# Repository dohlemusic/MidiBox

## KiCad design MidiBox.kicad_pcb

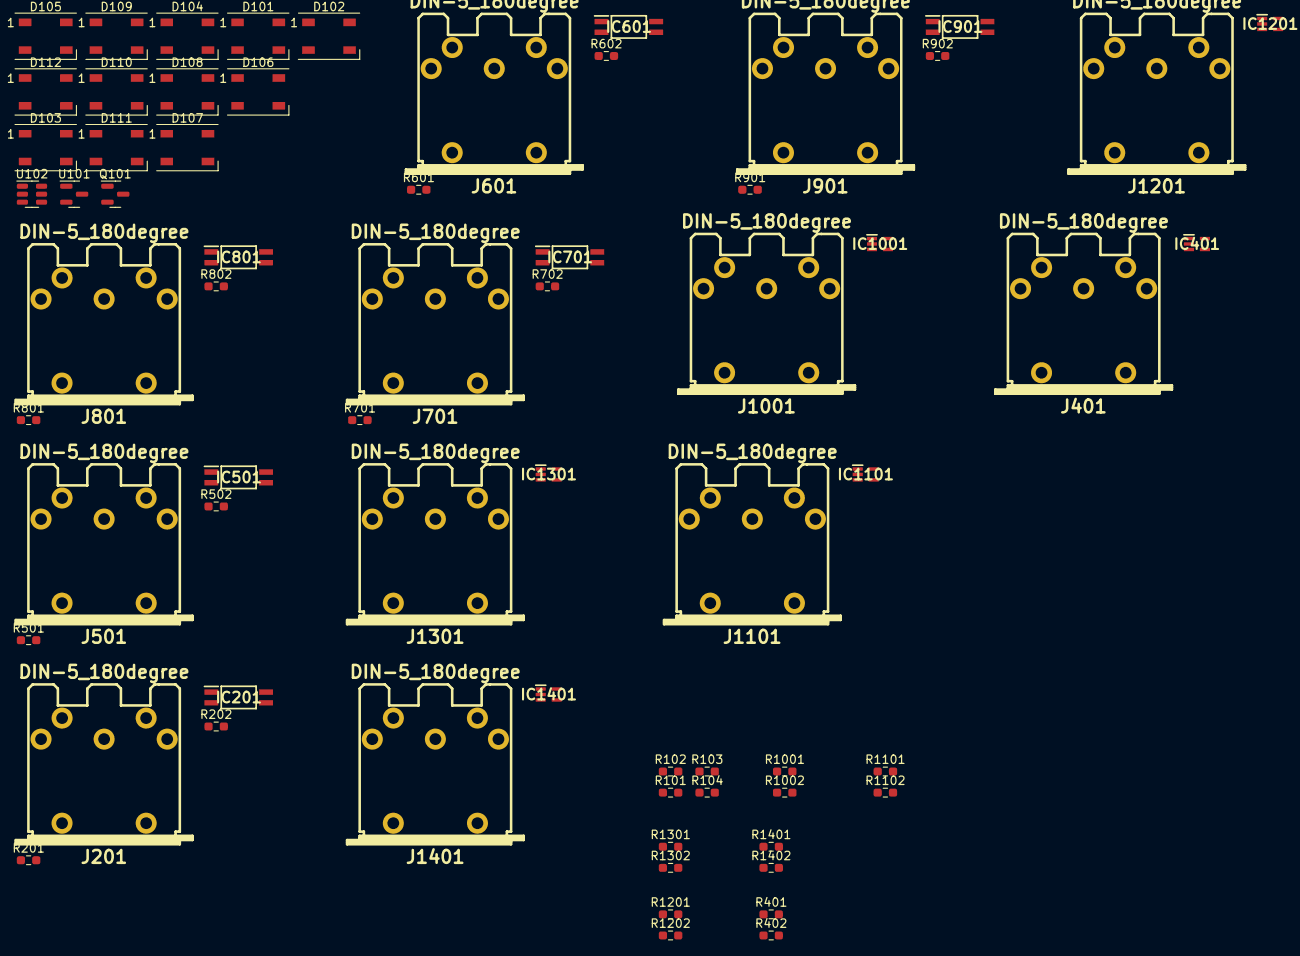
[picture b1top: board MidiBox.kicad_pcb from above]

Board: 2 copper layers, 67 parts (0 on the bottom side), 57 nets, no tracks yet.

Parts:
D101, D102, D103, D104, D105, D106, D107, D108, D109, D110, D111, D112: WS2812B; LED_WS2812B_PLCC4_5.0x5.0mm_P3.2mm
IC201, IC501, IC601, IC701, IC801, IC901: TLP293_GR-TPL,E; SOIC127P700X230-4N
IC401, IC1001, IC1101, IC1201, IC1301, IC1401: SN74AHC1G125DCKR; SOT65P210X110-5N
J201, J401, J501, J601, J701, J801, J901, J1001, J1101, J1201, J1301, J1401: DIN-5_180degree; MIDI_DIN5
Q101: AO3401A; SOT-23
R101: 470; R_0603_1608Metric_Pad0.98x0.95mm_HandSolder
R102: 4.7k; R_0603_1608Metric_Pad0.98x0.95mm_HandSolder
R103, R104: 22k; R_0603_1608Metric_Pad0.98x0.95mm_HandSolder
R201, R202, R401, R402, R501, R502, R601, R602, R701, R702, R801, R802, R901, R902, R1001, R1002, R1101, R1102, R1201, R1202, R1301, R1302, R1401, R1402: 220; R_0603_1608Metric_Pad0.98x0.95mm_HandSolder
U101: XC6206P332MR; SOT-23
U102: USBLC6-2SC6; SOT-23-6

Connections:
+3V3: Q101.2 (S), R202.2, R502.2, R602.2, R702.2, R802.2, R902.2, U101.2 (VO)
+5V: D101.1 (VDD), D102.1 (VDD), D103.1 (VDD), D104.1 (VDD), D105.1 (VDD), D106.1 (VDD), D107.1 (VDD), D108.1 (VDD), D109.1 (VDD), D110.1 (VDD), D111.1 (VDD), D112.1 (VDD), IC401.5 (VCC), IC1001.5 (VCC), IC1101.5 (VCC), IC1201.5 (VCC), IC1301.5 (VCC), IC1401.5 (VCC), R402.2, R1002.2, R1102.2, R1202.2, R1302.2, R1402.2, U101.3 (VI), U102.5 (VBUS)
GND: D101.3 (VSS), D102.3 (VSS), D103.3 (VSS), D104.3 (VSS), D105.3 (VSS), D106.3 (VSS), D107.3 (VSS), D108.3 (VSS), D109.3 (VSS), D110.3 (VSS), D111.3 (VSS), D112.3 (VSS), IC201.3 (EMITTER), IC401.1 (~OE), IC401.3 (GND), IC501.3 (EMITTER), IC601.3 (EMITTER), IC701.3 (EMITTER), IC801.3 (EMITTER), IC901.3 (EMITTER), IC1001.1 (~OE), IC1001.3 (GND), IC1101.1 (~OE), IC1101.3 (GND), IC1201.1 (~OE), IC1201.3 (GND), IC1301.1 (~OE), IC1301.3 (GND), IC1401.1 (~OE), IC1401.3 (GND), J401.2, J1001.2, J1101.2, J1201.2, J1301.2, J1401.2, R102.2, R103.2, R104.2, U101.1 (GND), U102.2 (GND)
MIDI_IN1: IC201.4 (COLLECTOR), R202.1
MIDI_IN2: IC501.4 (COLLECTOR), R502.1
MIDI_IN3: IC601.4 (COLLECTOR), R602.1
MIDI_IN4: IC701.4 (COLLECTOR), R702.1
MIDI_IN5: IC801.4 (COLLECTOR), R802.1
MIDI_IN6: IC901.4 (COLLECTOR), R902.1
unnamed: D101.2 (DOUT), D102.4 (DIN)
unnamed: D102.2 (DOUT), D103.4 (DIN)
unnamed: D103.2 (DOUT), D104.4 (DIN)
unnamed: D104.2 (DOUT), D105.4 (DIN)
unnamed: D105.2 (DOUT), D106.4 (DIN)
unnamed: D106.2 (DOUT), D107.4 (DIN)
unnamed: D107.2 (DOUT), D108.4 (DIN)
unnamed: D108.2 (DOUT), D109.4 (DIN)
unnamed: D109.2 (DOUT), D110.4 (DIN)
unnamed: D110.2 (DOUT), D111.4 (DIN)
unnamed: D111.2 (DOUT), D112.4 (DIN)
unnamed: IC201.1 (ANODE), R201.2
unnamed: IC201.2 (CATHODE), J201.5
unnamed: IC501.1 (ANODE), R501.2
unnamed: IC501.2 (CATHODE), J501.5
unnamed: IC601.1 (ANODE), R601.2
unnamed: IC601.2 (CATHODE), J601.5
unnamed: IC701.1 (ANODE), R701.2
unnamed: IC701.2 (CATHODE), J701.5
unnamed: IC801.1 (ANODE), R801.2
unnamed: IC801.2 (CATHODE), J801.5
unnamed: IC901.1 (ANODE), R901.2
unnamed: IC901.2 (CATHODE), J901.5
unnamed: IC401.4 (Y), R401.1
unnamed: IC1001.4 (Y), R1001.1
unnamed: IC1101.4 (Y), R1101.1
unnamed: IC1201.4 (Y), R1201.1
unnamed: IC1301.4 (Y), R1301.1
unnamed: IC1401.4 (Y), R1401.1
unnamed: J201.4, R201.1
unnamed: J401.4, R402.1
unnamed: J401.5, R401.2
unnamed: J501.4, R501.1
unnamed: J601.4, R601.1
unnamed: J701.4, R701.1
unnamed: J801.4, R801.1
unnamed: J901.4, R901.1
unnamed: J1001.4, R1002.1
unnamed: J1001.5, R1001.2
unnamed: J1101.4, R1102.1
unnamed: J1101.5, R1101.2
unnamed: J1201.4, R1202.1
unnamed: J1201.5, R1201.2
unnamed: J1301.4, R1302.1
unnamed: J1301.5, R1301.2
unnamed: J1401.4, R1402.1
unnamed: J1401.5, R1401.2
unnamed: Q101.1 (G), R101.2, R102.1

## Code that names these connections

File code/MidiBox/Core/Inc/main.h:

/* USER CODE BEGIN Header */
/**
  ******************************************************************************
  * @file           : main.h
  * @brief          : Header for main.c file.
  *                   This file contains the common defines of the application.
  ******************************************************************************
  * @attention
  *
  * Copyright (c) 2023 STMicroelectronics.
  * All rights reserved.
  *
  * This software is licensed under terms that can be found in the LICENSE file
  * in the root directory of this software component.
  * If no LICENSE file comes with this software, it is provided AS-IS.
  *
  ******************************************************************************
  */
/* USER CODE END Header */

/* Define to prevent recursive inclusion -------------------------------------*/
#ifndef __MAIN_H
#define __MAIN_H

#ifdef __cplusplus
extern "C" {
#endif

/* Includes ------------------------------------------------------------------*/
#include "stm32g0xx_hal.h"

/* Private includes ----------------------------------------------------------*/
/* USER CODE BEGIN Includes */

/* USER CODE END Includes */

/* Exported types ------------------------------------------------------------*/
/* USER CODE BEGIN ET */

/* USER CODE END ET */

/* Exported constants --------------------------------------------------------*/
/* USER CODE BEGIN EC */

/* USER CODE END EC */

/* Exported macro ------------------------------------------------------------*/
/* USER CODE BEGIN EM */

/* USER CODE END EM */

void HAL_TIM_MspPostInit(TIM_HandleTypeDef *htim);

/* Exported functions prototypes ---------------------------------------------*/
void Error_Handler(void);

/* USER CODE BEGIN EFP */

/* USER CODE END EFP */

/* Private defines -----------------------------------------------------------*/
#define MIDI_IN5_Pin GPIO_PIN_11
#define MIDI_IN5_GPIO_Port GPIOC
#define BTN_IN6_Pin GPIO_PIN_12
#define BTN_IN6_GPIO_Port GPIOC
#define WS2812B_Pin GPIO_PIN_1
#define WS2812B_GPIO_Port GPIOC
#define BTN_OUT6_Pin GPIO_PIN_3
#define BTN_OUT6_GPIO_Port GPIOC
#define MIDI_OUT6_Pin GPIO_PIN_0
#define MIDI_OUT6_GPIO_Port GPIOA
#define MIDI_IN6_Pin GPIO_PIN_1
#define MIDI_IN6_GPIO_Port GPIOA
#define MIDI_OUT5_Pin GPIO_PIN_2
#define MIDI_OUT5_GPIO_Port GPIOA
#define BTN_OUT5_Pin GPIO_PIN_3
#define BTN_OUT5_GPIO_Port GPIOA
#define MIDI_OUT4_Pin GPIO_PIN_4
#define MIDI_OUT4_GPIO_Port GPIOA
#define DISP_BRI_Pin GPIO_PIN_5
#define DISP_BRI_GPIO_Port GPIOA
#define BTN_OUT4_Pin GPIO_PIN_6
#define BTN_OUT4_GPIO_Port GPIOA
#define MIDI_OUT3_Pin GPIO_PIN_4
#define MIDI_OUT3_GPIO_Port GPIOC
#define BTN_OUT3_Pin GPIO_PIN_5
#define BTN_OUT3_GPIO_Port GPIOC
#define MIDI_OUT2_Pin GPIO_PIN_0
#define MIDI_OUT2_GPIO_Port GPIOB
#define BTN_OUT2_Pin GPIO_PIN_1
#define BTN_OUT2_GPIO_Port GPIOB
#define MIDI_OUT1_Pin GPIO_PIN_10
#define MIDI_OUT1_GPIO_Port GPIOB
#define BTN_OUT1_Pin GPIO_PIN_11
#define BTN_OUT1_GPIO_Port GPIOB
#define DISP_SCK_Pin GPIO_PIN_13
#define DISP_SCK_GPIO_Port GPIOB
#define DISP_MOSI_Pin GPIO_PIN_15
#define DISP_MOSI_GPIO_Port GPIOB
#define DISP_A0_Pin GPIO_PIN_8
#define DISP_A0_GPIO_Port GPIOA
#define DISP_RST_Pin GPIO_PIN_6
#define DISP_RST_GPIO_Port GPIOC
#define DISP_CS_Pin GPIO_PIN_7
#define DISP_CS_GPIO_Port GPIOC
#define ENC_CH1_Pin GPIO_PIN_8
#define ENC_CH1_GPIO_Port GPIOC
#define ENC_CH2_Pin GPIO_PIN_9
#define ENC_CH2_GPIO_Port GPIOC
#define ENC_BTN_Pin GPIO_PIN_0
#define ENC_BTN_GPIO_Port GPIOD
#define BTN_IN1_Pin GPIO_PIN_1
#define BTN_IN1_GPIO_Port GPIOD
#define MIDI_IN1_Pin GPIO_PIN_2
#define MIDI_IN1_GPIO_Port GPIOD
#define BTN_IN2_Pin GPIO_PIN_5
#define BTN_IN2_GPIO_Port GPIOD
#define MIDI_IN2_Pin GPIO_PIN_6
#define MIDI_IN2_GPIO_Port GPIOD
#define BTN_IN3_Pin GPIO_PIN_6
#define BTN_IN3_GPIO_Port GPIOB
#define MIDI_IN3_Pin GPIO_PIN_7
#define MIDI_IN3_GPIO_Port GPIOB
#define BTN_IN4_Pin GPIO_PIN_8
#define BTN_IN4_GPIO_Port GPIOB
#define MIDI_IN4_Pin GPIO_PIN_9
#define MIDI_IN4_GPIO_Port GPIOB
#define BTN_IN5_Pin GPIO_PIN_10
#define BTN_IN5_GPIO_Port GPIOC

/* USER CODE BEGIN Private defines */

/* USER CODE END Private defines */

#ifdef __cplusplus
}
#endif

#endif /* __MAIN_H */

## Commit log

2023-01-07 Add project stub
2023-01-07 Move MIDI to hierarchical sheets and wire it
2023-01-08 Finish IO design
